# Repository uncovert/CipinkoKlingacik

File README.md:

# ČipinkoKlingáčik

**A socketed Raspberry Pi Pico 2 voltage fault-injection carrier for supervised
hardware research.** Portable project/repository name: `cipinkoklingacik`.

**Release: `v0.1.0-alpha.2` · Hardware: C4 · Engineering prototype.**
The routed design passes static electrical/layout checks. **Firmware is not
implemented; no boards have been built or hardware-qualified.** This is not a
production-ready instrument or a guaranteed bypass of any device protection.

*Generic package models; the Pico is a disclosed form-factor proxy. Socket
height, colours and USB clearance are not mechanically approved.*

## What it provides

- A replaceable **Pico 2** on two 1×20 sockets; USB faces the board edge.
- Separate **MOSFET crowbar** and **3.3 V / 1.8 V current-bounded voltage selector**.
- Target disconnect, passive off discharge, open-drain reset and 3.3 V trigger input.
- Optional UART voltage translation and four-terminal current-measurement pads.
- A 100 × 85 mm, two-layer carrier with four M2.5 mounting positions.

The board uses established circuit techniques and manufacturer/KiCad assets;
it is a custom carrier, **not a fork of PicoGlitcher**. There is no SWD debugger
implementation. An external SWD probe and synchronization software are separate.

## Start here

| Need | Location |
| --- | --- |
| Open the design | [KiCad project](hardware/cipinkoklingacik.kicad_pro) · [hardware guide](hardware/README.md) |
| Read the circuit | [Electrical design](docs/DESIGN.md) · [schematic PDF](hardware/cipinkoklingacik.pdf) |
| Connect a target | [Wiring and SWD overview](docs/CONNECTING.md) |
| View the assembly | [3D views and PDF](hardware/visuals/README.md) |
| Review PCB evidence | [PCB review](hardware/PCB_REVIEW.md) · [review decisions](docs/REVIEW.md) |
| Inspect manufacturing data | [Prototype package](hardware/manufacturing/README.md) |
| Upload to JLCPCB | [Upload files, sourcing review and cost model](docs/JLCPCB.md) |
| Reproduce checks | [Build/check guide](docs/BUILD.md) |
| Understand remaining work | [Qualification checklist](docs/VALIDATION.md) · [parts policy](docs/PARTS.md) |

## Operating boundaries

- **10 mA total downstream load**, including target, bleeders and fitted interfaces.
  Both mux input branches retain **15 Ω** resistors; do not bypass them.
- Initial profiles: ≤100 nF / four dips or ≤1 µF / one dip, ≥20 ms between burst
  starts. At 100 nF the RC settling estimate is ~5.8 µs. **No settled 100 ns /
  100 nF promise.** Source labels are not calibrated target-pin voltages.
- Crowbar and target supply are different connectors. Externally powered crowbar
  targets leave the board's target-supply wire disconnected.
- **ARM ships open. No independent stuck-on timeout is fitted.** Use only
  expendable, authorized targets and qualify first with energy-limited dummy loads.
- Driver operation requires **4.90–5.25 V measured at VDD**. An arbitrary USB
  source/cable is not guaranteed to meet this. No hot-plug or misplug protection.

## Quick verification

```sh
python3 -m unittest discover -s tests -v
python3 scripts/design_calculations.py
```

These dependency-free checks inspect the included sources and exports; they
are **not a fresh KiCad run or hardware validation**. See [BUILD.md](docs/BUILD.md)
for full schematic regeneration, ERC, strict DRC/parity, exports and renders.
Never mix fabrication files from different manifests.

## Release and licensing

[Release notes](docs/RELEASE.md) describe the alpha handoff and local packaging.
Supplier sourcing/rotation, socket/USB fit, firmware, transient, thermal and
waveform qualification remain open. No components or boards have been ordered.

Original hardware is **CERN-OHL-P-2.0**; original software and prose are **MIT**.
Vendored KiCad assets retain their upstream licences and exceptions. See
[LICENSE](LICENSE), [NOTICE.md](NOTICE.md) and [CONTRIBUTING.md](CONTRIBUTING.md).

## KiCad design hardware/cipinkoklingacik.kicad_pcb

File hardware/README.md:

# ČipinkoKlingáčik hardware — C4

**Engineering-prototype design files, not qualified hardware.** Open
[`cipinkoklingacik.kicad_pro`](cipinkoklingacik.kicad_pro) in **KiCad 10**.
The A2 schematic uses named connections and project-local pinned libraries.
No library download is needed to inspect its connectivity.

## Authoritative sources and exports

| Files | Purpose |
| --- | --- |
| `cipinkoklingacik.kicad_pcb` | Authoritative, fully routed PCB; edit in PCB Editor |
| `cipinkoklingacik.kicad_sch` / `.kicad_sym` | Generator-owned schematic/symbols |
| `cipinkoklingacik.kicad_pro`, `fp-lib-table`, `sym-lib-table` | Project/rules/library mapping |
| `CipinkoKlingacik.pretty/`, `vendor/` | Pinned footprints/primitives, provenance and licences |
| [Schematic PDF](cipinkoklingacik.pdf) / [preview](cipinkoklingacik-schematic.png) | Review drawings |
| [Full DRC](cipinkoklingacik-drc.json), [ERC](cipinkoklingacik-erc.rpt), [status](cipinkoklingacik-pcb-status.json) | Static check evidence and source hashes |
| [Connectivity](cipinkoklingacik-connectivity.json), `cipinkoklingacik.net` | Intended contract and actual KiCad export |
| [Baseline BOM](cipinkoklingacik-bom.csv), [all parts](cipinkoklingacik-parts-all.csv) | Exact candidate parts and native DNP state |
| [Manufacturing](manufacturing/README.md) | Baseline Gerber/drill/stencil/BOM/placement package |
| [Visuals](visuals/README.md) | Illustrative assembled/top/bottom/service views |

The board has **92 schematic footprints + four mechanical footprints**.
Baseline population: **68 SMT + seven hand-fit references**, eight bare probe
pads, and nine DNP references: **U8, C18, JP3–JP5, R20, R31, R40, R41**.
R39=0 Ω is fitted. JP2 ARM has **no cap fitted**. Module headers/sockets and loose
caps are separate accessories, not additional SMT rows.

## Source ownership / maintenance

- **PCB:** authoritative and not generator-owned. There is no board-regeneration
  script in this release. Preserve intentional edits; see [BUILD.md](../docs/BUILD.md).
- **Schematic:** edit `scripts/generate_kicad_schematic.py` and
  `scripts/hardware_parts.py`; normal regeneration overwrites schematic, local
  symbols, library tables, connectivity and BOMs. This is not a round-trip editor.
- Stable UUIDs are deliberately retained across the project rename. The legacy
  UUID seed is an internal identifier, not an old project output or PCB generator.
- Footprint upgrades are explicit operations; normal regeneration never updates
  pinned library geometry. Follow [vendor/README.md](vendor/README.md).
- After a PCB edit: run strict checks, refresh return review, rerun strict
  checks, regenerate renders and prototype exports, then run all tests.

## Check interpretation

KiCad 10.0.7 evidence: **ERC 0 errors / 0 warnings**; **PCB DRC 0 violations /
0 unconnected / 0 schematic parity issues**; no ignored PCB checks or exclusions.
The regression suite rejects new ignores and pins the reviewed severity settings.

ERC retains four disclosed standard ignores: single-use global labels, four-way
wire junctions, SPICE-model issues and footprint-filter mismatch. This local-label,
single-sheet, no-SPICE custom-symbol capture does not use global labels or
footprint filters; PCB footprint-filter checking is enabled. Static checks are
not electrical, thermal, assembly or firmware qualification.

## Important net aliases

| Alias | Meaning |
| --- | --- |
| `GL` | Separate crowbar drain — **not** target supply |
| `TVDD` / `T_PRE` | Target supply / pre-shunt supply |
| `VH` / `VL` | High/low upstream reservoirs |
| `MVCC` / `HOLD` | Retained mux supply / its held input |
| `MY0` / `MY1` / `MZ` | Mux input/output nodes |
| `MUX_CMD` / `MUX_S` | GP5 command / mux select |
| `CB_PULSE` / `ARM_EN` | GP2 pulse / GP8 driver arm |
| `TGT_ON` / `REN` | GP4 disconnect / GP10 rail enable |
| `RST_ASSERT` / `RST_T` | Reset control / open-drain target reset |
| `TRIG_IN` / `TRIG_OUT` | Raw trigger input / conditioned GP3 input |
| `UART_OE` / `UVCCB` | GP9 UART disable / isolated UART target reference |
| `ISENSE_P` / `ISENSE_N` | Separate R20 sense terminals; differential probing only |

Full pin allocation, timing and power states are in [DESIGN.md](../docs/DESIGN.md).
Read [PCB_REVIEW.md](PCB_REVIEW.md) and [VALIDATION.md](../docs/VALIDATION.md)
before any order or target connection.

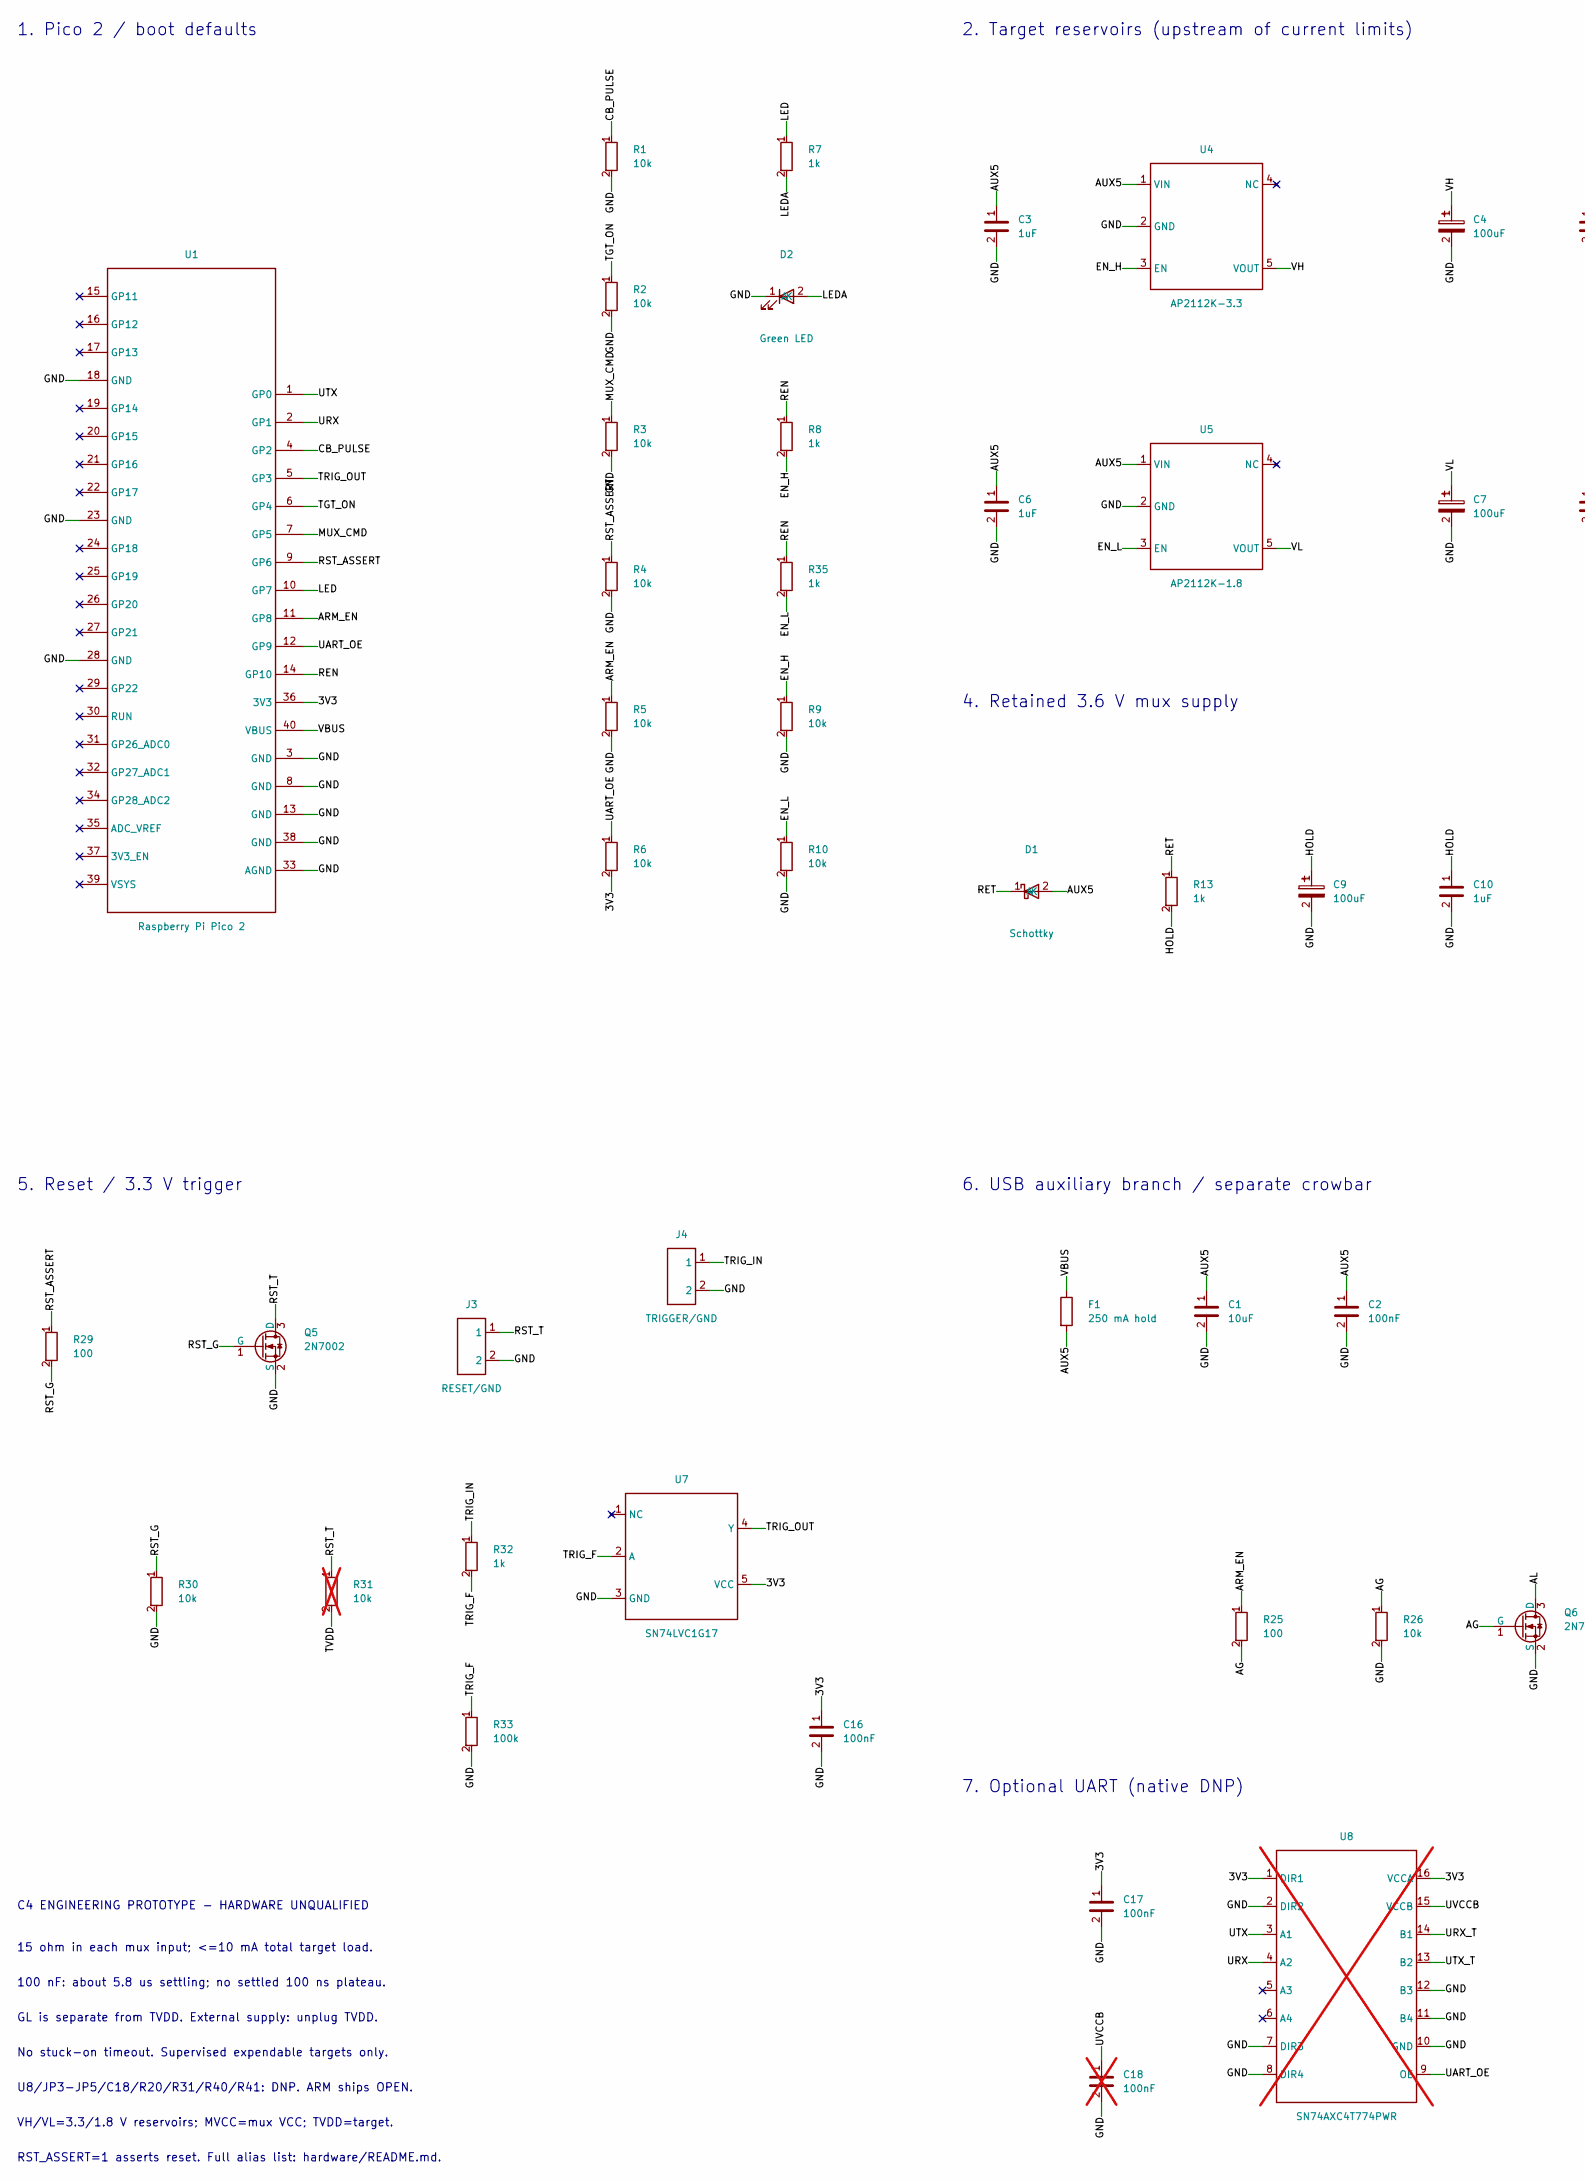
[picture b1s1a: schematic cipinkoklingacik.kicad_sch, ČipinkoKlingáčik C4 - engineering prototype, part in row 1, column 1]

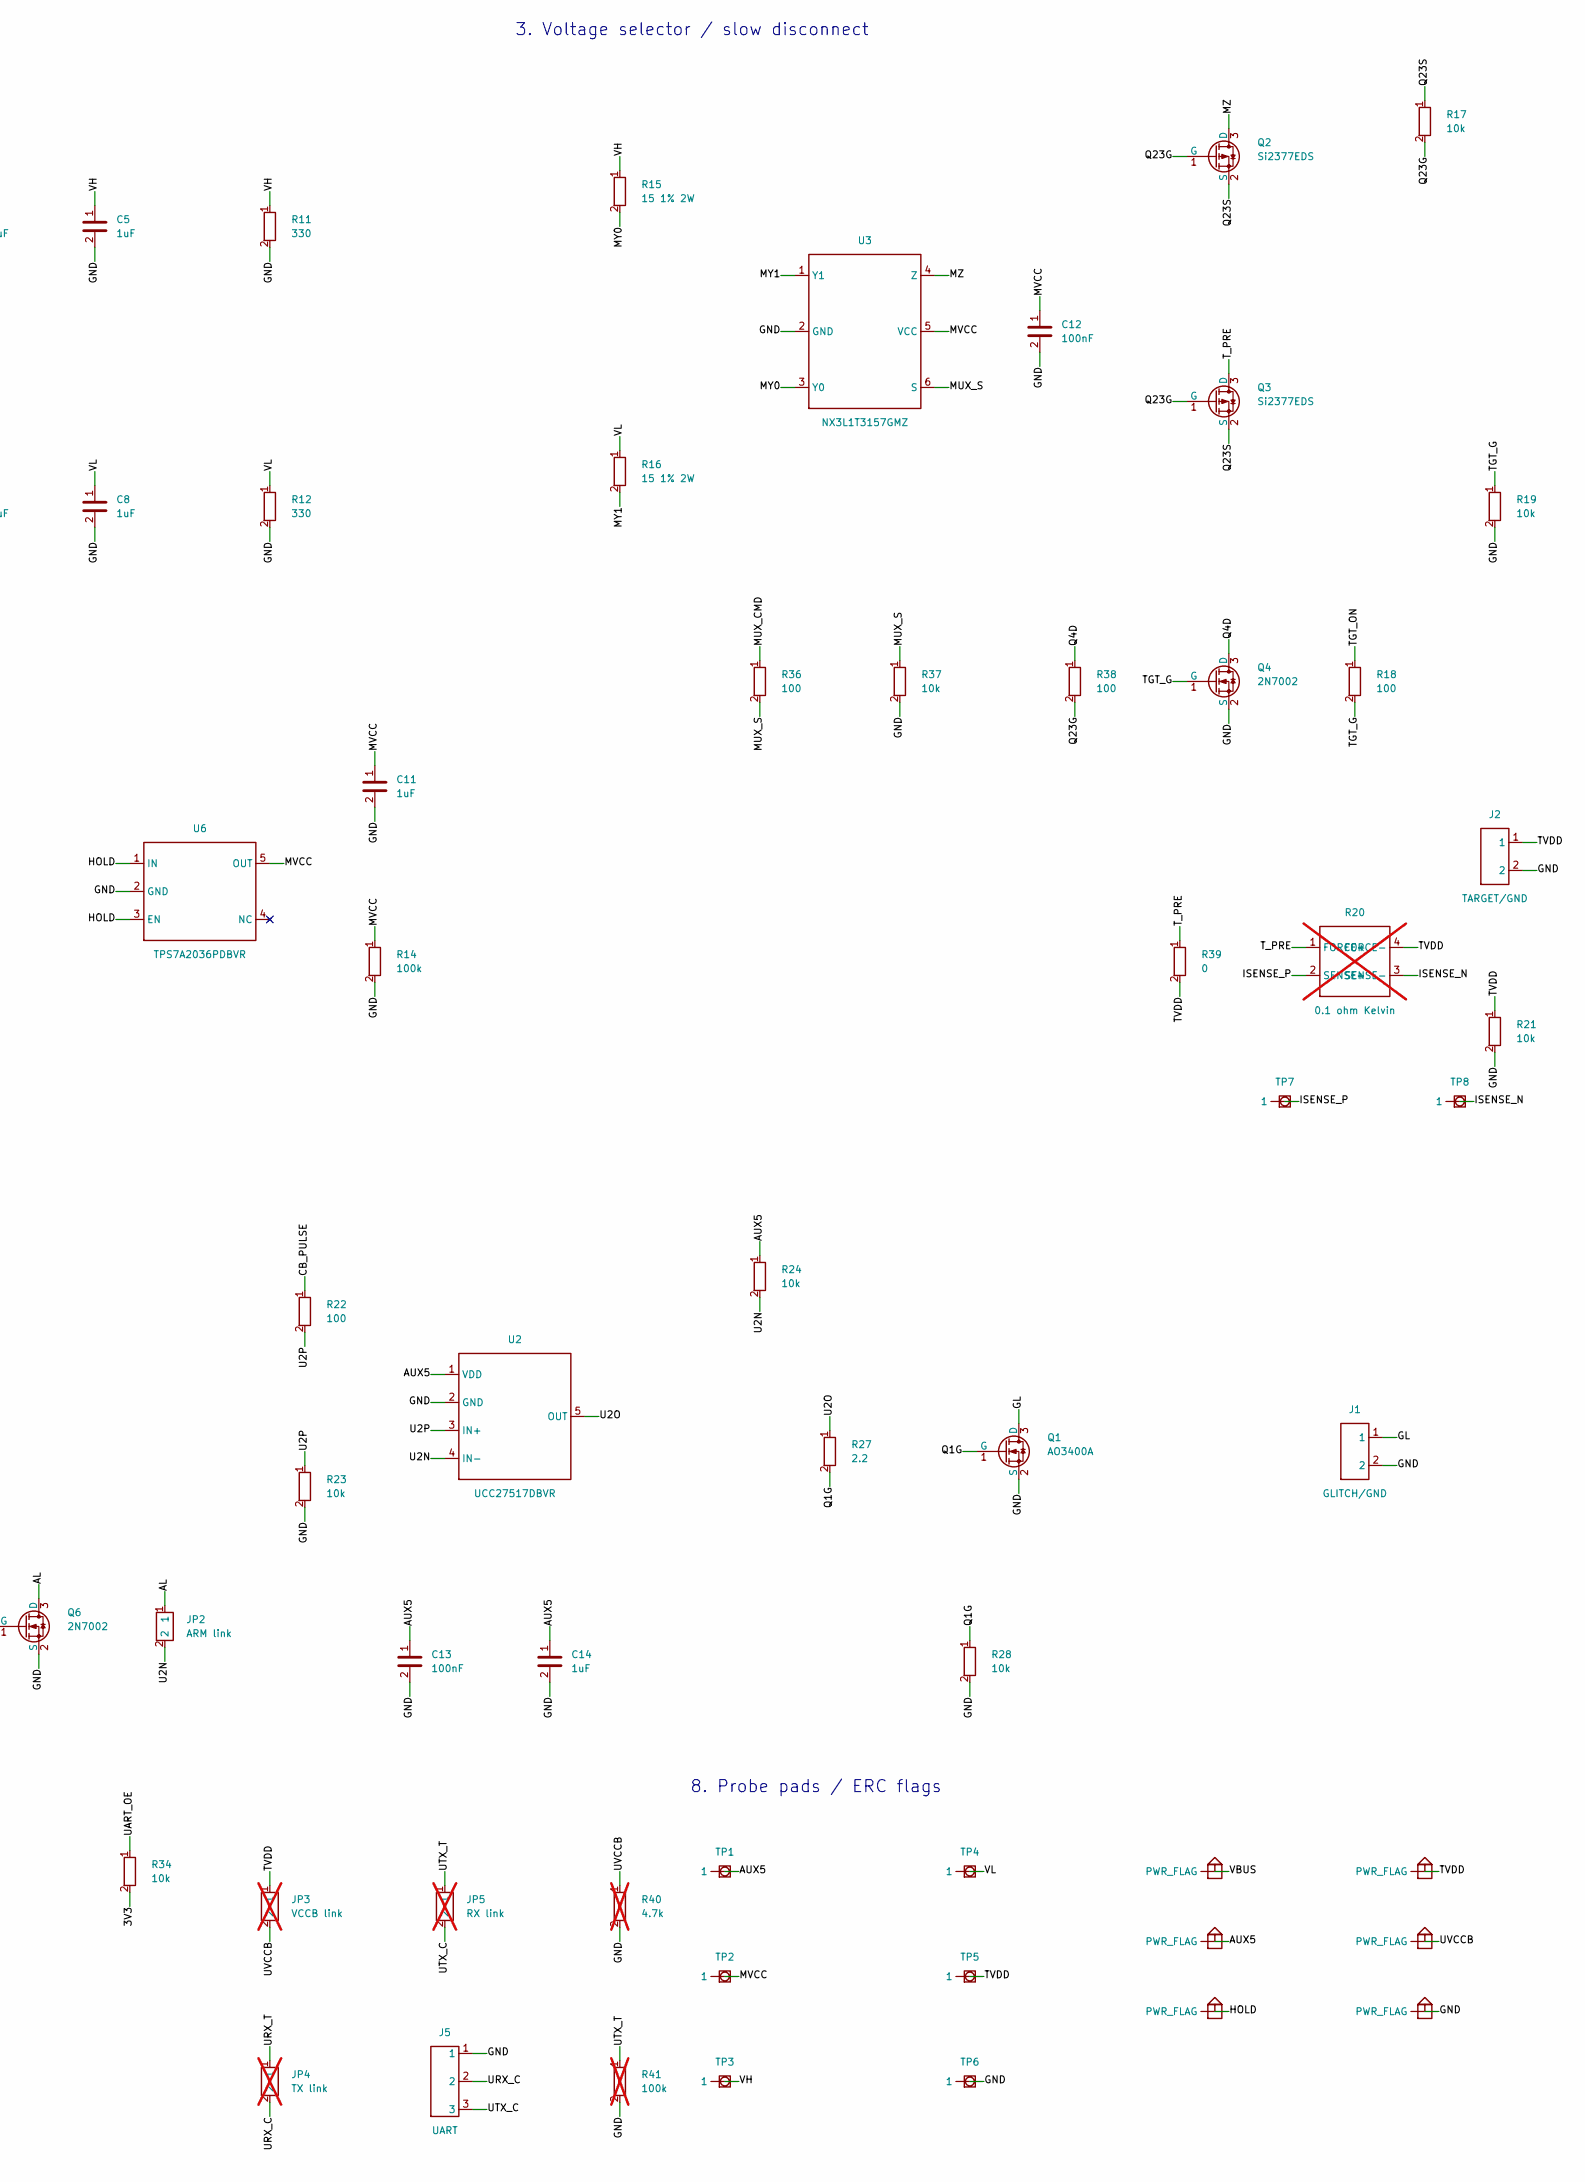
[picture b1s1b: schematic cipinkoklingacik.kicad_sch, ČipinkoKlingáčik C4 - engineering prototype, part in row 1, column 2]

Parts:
C1: 10uF; C_1206_3216Metric; MPN GRM31CR71C106KA12L; LCSC C97954
C2, C12, C13, C16, C17: 100nF; C_0805_2012Metric; MPN CC0805KRX7R9BB104; LCSC C49678
C3, C5, C6, C8, C10, C11, C14: 1uF; C_0805_2012Metric; MPN GRM21BR71C105KA01L; LCSC C77079
C4, C7, C9: 100uF; CP_Elec_6.3x5.8; MPN EEE-FK1C101P; LCSC C128532
C18: 100nF; C_0805_2012Metric; MPN CC0805KRX7R9BB104; LCSC C49678; not fitted
D1: Schottky; D_SOD-323; MPN BAT54WS-7-F; LCSC C124205
D2: Green LED; LED_0805_2012Metric; MPN LTST-C170KGKT; LCSC C98221
F1: 250 mA hold; Fuse_1206_3216Metric; MPN 1206L025YR; LCSC C99561
J1: GLITCH/GND; PinHeader_1x02_P2.54mm_Vertical; MPN TSW-102-07-G-S
J2: TARGET/GND; PinHeader_1x02_P2.54mm_Vertical; MPN TSW-102-07-G-S
J3: RESET/GND; PinHeader_1x02_P2.54mm_Vertical; MPN TSW-102-07-G-S
J4: TRIGGER/GND; PinHeader_1x02_P2.54mm_Vertical; MPN TSW-102-07-G-S
J5: UART; PinHeader_1x03_P2.54mm_Vertical; MPN TSW-103-07-G-S
JP2: ARM link; PinHeader_1x02_P2.54mm_Vertical; MPN TSW-102-07-G-S
JP3: VCCB link; PinHeader_1x02_P2.54mm_Vertical; MPN TSW-102-07-G-S; not fitted
JP4: TX link; PinHeader_1x02_P2.54mm_Vertical; MPN TSW-102-07-G-S; not fitted
JP5: RX link; PinHeader_1x02_P2.54mm_Vertical; MPN TSW-102-07-G-S; not fitted
Q1: AO3400A; SOT-23; MPN AO3400A; LCSC C20917
Q2, Q3: Si2377EDS; SOT-23; MPN Si2377EDS-T1-GE3; LCSC C143698
Q4, Q5, Q6: 2N7002; SOT-23; MPN 2N7002,215; LCSC C65189
R1, R2, R3, R4, R5, R6, R9, R10, R17, R19, R21, R23, R24, R26, R28, R30, R34, R37: 10k; R_0805_2012Metric; MPN 0805W8F1002T5E; LCSC C17414
R7, R8, R13, R32, R35: 1k; R_0805_2012Metric; MPN 0805W8F1001T5E; LCSC C17513
R11, R12: 330; R_0805_2012Metric; MPN 0805W8F3300T5E; LCSC C17630
R14, R33: 100k; R_0805_2012Metric; MPN 0805W8F1003T5E; LCSC C149504
R15, R16: 15 1% 2W; R_2512_6332Metric; MPN RC2512FK-7W15RL; LCSC C6639259
R18, R22, R25, R29, R36, R38: 100; R_0805_2012Metric; MPN 0805W8F1000T5E; LCSC C17408
R20: 0.1 ohm Kelvin; R_Shunt_Vishay_WSK2512_6332Metric_T1.19mm; MPN WSK2512R1000FEA; not fitted
R27: 2.2; R_0805_2012Metric; MPN 0805W8F220KT5E; LCSC C17521
R31: 10k; R_0805_2012Metric; MPN 0805W8F1002T5E; LCSC C17414; not fitted
R39: 0; R_1206_3216Metric; MPN 1206W4F0000T5E; LCSC C17888
R40: 4.7k; R_0805_2012Metric; MPN RC0805FR-074K7L; not fitted
R41: 100k; R_0805_2012Metric; MPN RC0805FR-07100KL; not fitted
TP1: AUX_5V; TestPoint_Pad_D1.5mm; MPN PCB_PAD
TP2: MUX_VCC; TestPoint_Pad_D1.5mm; MPN PCB_PAD
TP3: VHIGH; TestPoint_Pad_D1.5mm; MPN PCB_PAD
TP4: VLOW; TestPoint_Pad_D1.5mm; MPN PCB_PAD
TP5: TARGET_VDD; TestPoint_Pad_D1.5mm; MPN PCB_PAD
TP6: GND; TestPoint_Pad_D1.5mm; MPN PCB_PAD
TP7: ISENSE_P; TestPoint_Pad_D1.5mm; MPN PCB_PAD
TP8: ISENSE_N; TestPoint_Pad_D1.5mm; MPN PCB_PAD
U1: Raspberry Pi Pico 2; RaspberryPi_Pico_Common_THT; MPN SC1631
U2: UCC27517DBVR; SOT-23-5; MPN UCC27517DBVR; LCSC C99395
U3: NX3L1T3157GMZ; SOT-886; MPN NX3L1T3157GMZ; LCSC C1870392
U4: AP2112K-3.3; SOT-23-5; MPN AP2112K-3.3TRG1; LCSC C51118
U5: AP2112K-1.8; SOT-23-5; MPN AP2112K-1.8TRG1; LCSC C176944
U6: TPS7A2036PDBVR; SOT-23-5; MPN TPS7A2036PDBVR; LCSC C2873626
U7: SN74LVC1G17; SOT-23-5; MPN SN74LVC1G17DBVR; LCSC C7836
U8: SN74AXC4T774PWR; TSSOP-16_4.4x5mm_P0.65mm; MPN SN74AXC4T774PWR; not fitted

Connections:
/3V3: C16.1, C17.1, R6.2, R34.2, U1.36 (3V3), U7.5 (VCC), U8.1 (DIR1), U8.16 (VCCA)
/AG: Q6.1 (G), R25.2, R26.1
/AL: JP2.1, Q6.3 (D)
/ARM_EN: R5.1, R25.1, U1.11 (GP8)
/AUX5: C1.1, C2.1, C3.1, C6.1, C13.1, C14.1, D1.2 (A), F1.2, R24.1, TP1.1, U2.1 (VDD), U4.1 (VIN), U5.1 (VIN)
/CB_PULSE: R1.1, R22.1, U1.4 (GP2)
/EN_H: R8.2, R9.1, U4.3 (EN)
/EN_L: R10.1, R35.2, U5.3 (EN)
/GL: J1.1, Q1.3 (D)
/GND: C1.2, C2.2, C3.2, C4.2, C5.2, C6.2, C7.2, C8.2, C9.2, C10.2, C11.2, C12.2, C13.2, C14.2, C16.2, C17.2, C18.2, D2.1 (K), J1.2, J2.2, J3.2, J4.2, J5.1, Q1.2 (S), Q4.2 (S), Q5.2 (S), Q6.2 (S), R1.2, R2.2, R3.2, R4.2, R5.2, R9.2, R10.2, R11.2, R12.2, R14.2, R19.2, R21.2, R23.2, R26.2, R28.2, R30.2, R33.2, R37.2, R40.2, R41.2, TP6.1, U1.3 (GND), U1.8 (GND), U1.13 (GND), U1.18 (GND), U1.23 (GND), U1.28 (GND), U1.33 (AGND), U1.38 (GND), U2.2 (GND), U3.2 (GND), U4.2 (GND), U5.2 (GND), U6.2 (GND), U7.3 (GND), U8.2 (DIR2), U8.7 (DIR3), U8.8 (DIR4), U8.10 (GND), U8.11 (B4), U8.12 (B3)
/HOLD: C9.1, C10.1, R13.2, U6.1 (IN), U6.3 (EN)
/ISENSE_N: R20.3 (SENSE-), TP8.1
/ISENSE_P: R20.2 (SENSE+), TP7.1
/LED: R7.1, U1.10 (GP7)
/LEDA: D2.2 (A), R7.2
/MUX_CMD: R3.1, R36.1, U1.7 (GP5)
/MUX_S: R36.2, R37.1, U3.6 (S)
/MVCC: C11.1, C12.1, R14.1, TP2.1, U3.5 (VCC), U6.5 (OUT)
/MY0: R15.2, U3.3 (Y0)
/MY1: R16.2, U3.1 (Y1)
/MZ: Q2.3 (D), U3.4 (Z)
/Q1G: Q1.1 (G), R27.2, R28.1
/Q4D: Q4.3 (D), R38.1
/Q23G: Q2.1 (G), Q3.1 (G), R17.2, R38.2
/Q23S: Q2.2 (S), Q3.2 (S), R17.1
/REN: R8.1, R35.1, U1.14 (GP10)
/RET: D1.1 (K), R13.1
/RST_ASSERT: R4.1, R29.1, U1.9 (GP6)
/RST_G: Q5.1 (G), R29.2, R30.1
/RST_T: J3.1, Q5.3 (D), R31.1
/TGT_G: Q4.1 (G), R18.2, R19.1
/TGT_ON: R2.1, R18.1, U1.6 (GP4)
/TRIG_F: R32.2, R33.1, U7.2 (A)
/TRIG_IN: J4.1, R32.1
/TRIG_OUT: U1.5 (GP3), U7.4 (Y)
/TVDD: J2.1, JP3.1, R20.4 (FORCE-), R21.1, R31.2, R39.2, TP5.1
/T_PRE: Q3.3 (D), R20.1 (FORCE+), R39.1
/U2N: JP2.2, R24.2, U2.4 (IN-)
/U2O: R27.1, U2.5 (OUT)
/U2P: R22.2, R23.1, U2.3 (IN+)
/UART_OE: R6.1, R34.1, U1.12 (GP9), U8.9 (OE)
/URX: U1.2 (GP1), U8.4 (A2)
/URX_C: J5.2, JP4.2
/URX_T: JP4.1, U8.14 (B1)
/UTX: U1.1 (GP0), U8.3 (A1)
/UTX_C: J5.3, JP5.2
/UTX_T: JP5.1, R41.1, U8.13 (B2)
/UVCCB: C18.1, JP3.2, R40.1, U8.15 (VCCB)
/VBUS: F1.1, U1.40 (VBUS)
/VH: C4.1, C5.1, R11.1, R15.1, TP3.1, U4.5 (VOUT)
/VL: C7.1, C8.1, R12.1, R16.1, TP4.1, U5.5 (VOUT)

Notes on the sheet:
1. Pico 2 / boot defaults
2. Target reservoirs (upstream of current limits)
3. Voltage selector / slow disconnect
4. Retained 3.6 V mux supply
5. Reset / 3.3 V trigger
6. USB auxiliary branch / separate crowbar
7. Optional UART (native DNP)
8. Probe pads / ERC flags
C4 ENGINEERING PROTOTYPE - HARDWARE UNQUALIFIED
15 ohm in each mux input; <=10 mA total target load.
100 nF: about 5.8 us settling; no settled 100 ns plateau.
GL is separate from TVDD. External supply: unplug TVDD.
No stuck-on timeout. Supervised expendable targets only.
U8/JP3-JP5/C18/R20/R31/R40/R41: DNP. ARM ships OPEN.
VH/VL=3.3/1.8 V reservoirs; MVCC=mux VCC; TVDD=target.
RST_ASSERT=1 asserts reset. Full alias list: hardware/README.md.

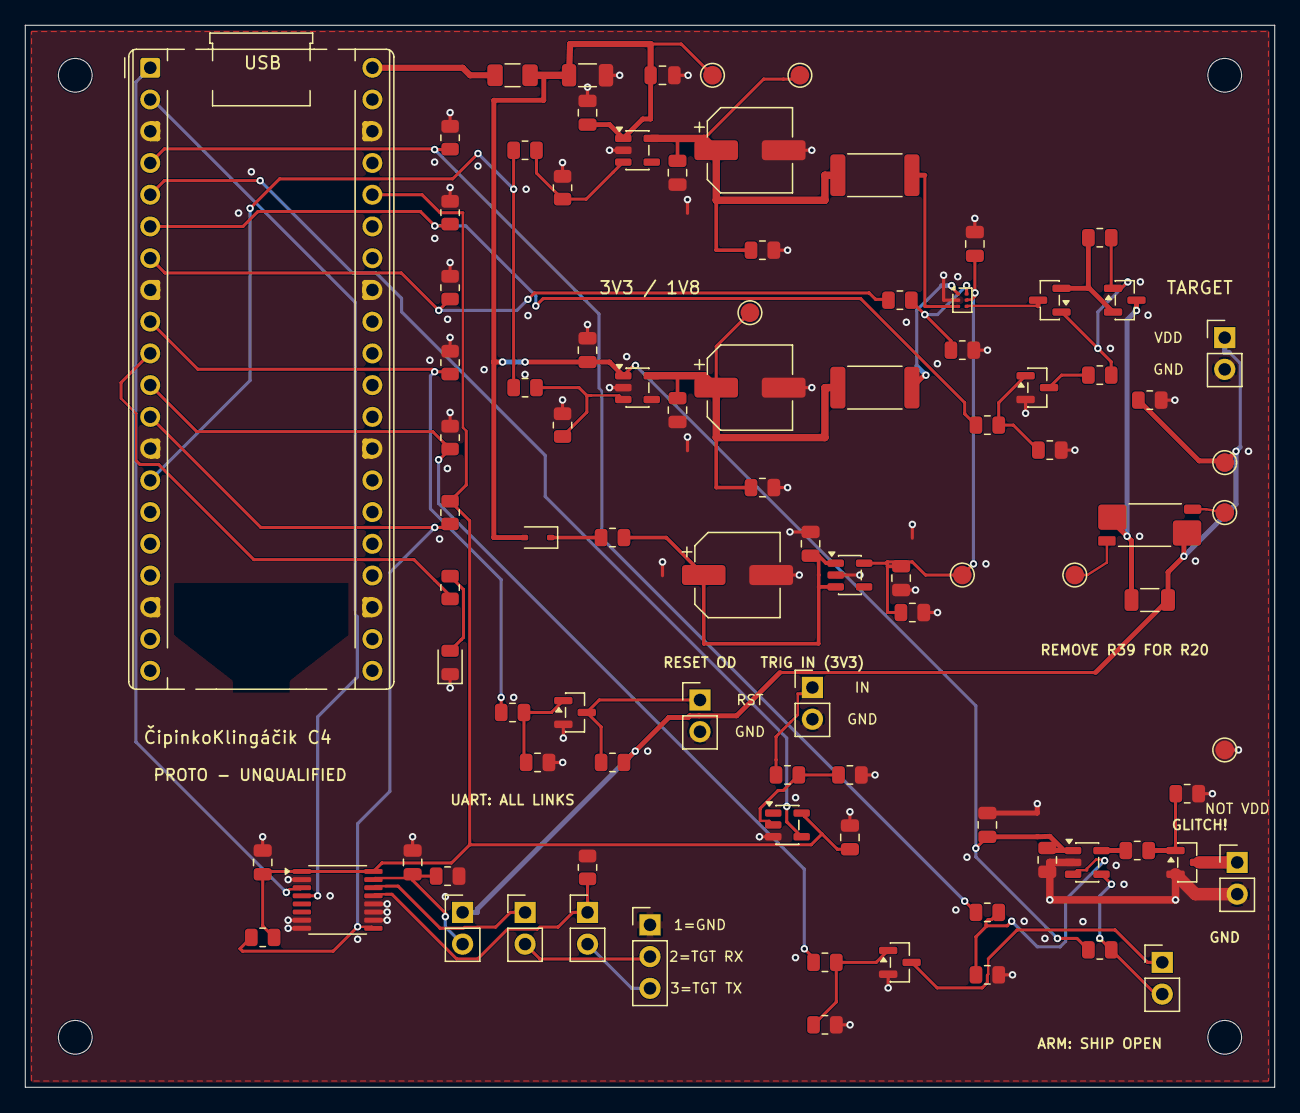
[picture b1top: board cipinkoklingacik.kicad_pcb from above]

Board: 2 copper layers, 100.0 x 85.0 mm, 96 parts (0 on the bottom side), 51 nets.

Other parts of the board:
H1, H2, H3, H4: M2.5 NPTH; MountingHole_2.7mm_M2.5

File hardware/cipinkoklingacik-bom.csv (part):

Reference,Value,MPN,Manufacturer,Footprint,DNP,Assembly,Requirement,Datasheet,LCSC
U1,Raspberry Pi Pico 2,SC1631,Raspberry Pi,CipinkoKlingacik:RaspberryPi_Pico_Common_THT,no,Module/hand-fit,Pico 2 without headers; hand-fit 2x 1x20 sockets and module headers,https://datasheets.raspberrypi.com/pico/pico-2-datasheet.pdf,
R1,10k,0805W8F1002T5E,UNI-ROYAL,CipinkoKlingacik:R_0805_2012Metric,no,SMT,"1%, 0.125 W; gate pulse rating requires check",https://www.lcsc.com/datasheet/lcsc_datasheet_2411221126_UNI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,C17414
R2,10k,0805W8F1002T5E,UNI-ROYAL,CipinkoKlingacik:R_0805_2012Metric,no,SMT,"1%, 0.125 W; gate pulse rating requires check",https://www.lcsc.com/datasheet/lcsc_datasheet_2411221126_UNI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,C17414
R3,10k,0805W8F1002T5E,UNI-ROYAL,CipinkoKlingacik:R_0805_2012Metric,no,SMT,"1%, 0.125 W; gate pulse rating requires check",https://www.lcsc.com/datasheet/lcsc_datasheet_2411221126_UNI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,C17414
R4,10k,0805W8F1002T5E,UNI-ROYAL,CipinkoKlingacik:R_0805_2012Metric,no,SMT,"1%, 0.125 W; gate pulse rating requires check",https://www.lcsc.com/datasheet/lcsc_datasheet_2411221126_UNI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,C17414
R5,10k,0805W8F1002T5E,UNI-ROYAL,CipinkoKlingacik:R_0805_2012Metric,no,SMT,"1%, 0.125 W; gate pulse rating requires check",https://www.lcsc.com/datasheet/lcsc_datasheet_2411221126_UNI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,C17414
R6,10k,0805W8F1002T5E,UNI-ROYAL,CipinkoKlingacik:R_0805_2012Metric,no,SMT,"1%, 0.125 W; gate pulse rating requires check",https://www.lcsc.com/datasheet/lcsc_datasheet_2411221126_UNI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,C17414
R7,1k,0805W8F1001T5E,UNI-ROYAL,CipinkoKlingacik:R_0805_2012Metric,no,SMT,"1%, 0.125 W; gate pulse rating requires check",https://www.lcsc.com/datasheet/lcsc_datasheet_2411221126_UNI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,C17513
D2,Green LED,LTST-C170KGKT,Lite-On,CipinkoKlingacik:LED_0805_2012Metric,no,SMT,Green LED; K1 A2; software status only,https://optoelectronics.liteon.com/upload/download/DS22-2000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,C98221
R8,1k,0805W8F1001T5E,UNI-ROYAL,CipinkoKlingacik:R_0805_2012Metric,no,SMT,"1%, 0.125 W; gate pulse rating requires check",https://www.lcsc.com/datasheet/lcsc_datasheet_2411221126_UNI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,C17513
R9,10k,0805W8F1002T5E,UNI-ROYAL,CipinkoKlingacik:R_0805_2012Metric,no,SMT,"1%, 0.125 W; gate pulse rating requires check",https://www.lcsc.com/datasheet/lcsc_datasheet_2411221126_UNI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,C17414
R10,10k,0805W8F1002T5E,UNI-ROYAL,CipinkoKlingacik:R_0805_2012Metric,no,SMT,"1%, 0.125 W; gate pulse rating requires check",https://www.lcsc.com/datasheet/lcsc_datasheet_2411221126_UNI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,C17414
R35,1k,0805W8F1001T5E,UNI-ROYAL,CipinkoKlingacik:R_0805_2012Metric,no,SMT,"1%, 0.125 W; gate pulse rating requires check",https://www.lcsc.com/datasheet/lcsc_datasheet_2411221126_UNI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,C17513
F1,250 mA hold,1206L025YR,Littelfuse,CipinkoKlingacik:Fuse_1206_3216Metric,no,SMT,"250 mA hold, 500 mA trip, 16 V PTC; 100 A fault rating; R1max 2.3 ohm; 80 ms max trip at 8 A, NOT precision limiting; qualify inrush/drop",https://www.lcsc.com/datasheet/lcsc_datasheet_2304140030_Lit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,C99561
C1,10uF,GRM31CR71C106KA12L,Murata,CipinkoKlingacik:C_1206_3216Metric,no,SMT,"10 uF, 16 V, X7R, 10%; check DC bias",https://www.murata.com/en-us/products/capacitor/mlcc,C97954
C2,100nF,CC0805KRX7R9BB104,Yageo,CipinkoKlingacik:C_0805_2012Metric,no,SMT,"100 nF, 50 V, X7R, 10%",https://www.lcsc.com/datasheet/lcsc_datasheet_2304140030_YAG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,C49678
U2,UCC27517DBVR,UCC27517DBVR,Texas Instruments,CipinkoKlingacik:SOT-23-5,no,SMT,4.90-5.25 V measured at VDD before arm,https://www.ti.com/lit/ds/symlink/ucc27517.pdf,C99395
C13,100nF,CC0805KRX7R9BB104,Yageo,CipinkoKlingacik:C_0805_2012Metric,no,SMT,"100 nF, 50 V, X7R, 10%",https://www.lcsc.com/datasheet/lcsc_datasheet_2304140030_YAG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,C49678
C14,1uF,GRM21BR71C105KA01L,Murata,CipinkoKlingacik:C_0805_2012Metric,no,SMT,"1 uF, 16 V, X7R, 10%; verify >=0.47 uF at bias",https://www.murata.com/en-us/products/capacitor/mlcc,C77079
R22,100,0805W8F1000T5E,UNI-ROYAL,CipinkoKlingacik:R_0805_2012Metric,no,SMT,"1%, 0.125 W; gate pulse rating requires check",https://www.lcsc.com/datasheet/lcsc_datasheet_2411221126_UNI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,C17408
R23,10k,0805W8F1002T5E,UNI-ROYAL,CipinkoKlingacik:R_0805_2012Metric,no,SMT,"1%, 0.125 W; gate pulse rating requires check",https://www.lcsc.com/datasheet/lcsc_datasheet_2411221126_UNI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,C17414
R24,10k,0805W8F1002T5E,UNI-ROYAL,CipinkoKlingacik:R_0805_2012Metric,no,SMT,"1%, 0.125 W; gate pulse rating requires check",https://www.lcsc.com/datasheet/lcsc_datasheet_2411221126_UNI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,C17414
Q6,2N7002,"2N7002,215",Nexperia,CipinkoKlingacik:SOT-23,no,SMT,G1 S2 D3,https://assets.nexperia.com/documents/data-sheet/2N7002.pdf,C65189
R25,100,0805W8F1000T5E,UNI-ROYAL,CipinkoKlingacik:R_0805_2012Metric,no,SMT,"1%, 0.125 W; gate pulse rating requires check",https://www.lcsc.com/datasheet/lcsc_datasheet_2411221126_UNI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,C17408
R26,10k,0805W8F1002T5E,UNI-ROYAL,CipinkoKlingacik:R_0805_2012Metric,no,SMT,"1%, 0.125 W; gate pulse rating requires check",https://www.lcsc.com/datasheet/lcsc_datasheet_2411221126_UNI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,C17414
JP2,ARM link,TSW-102-07-G-S,Samtec,CipinkoKlingacik:PinHeader_1x02_P2.54mm_Vertical,no,THT/hand-fit,2.54 mm header; pin1 marked; hand-fit; removable shunts separate,https://suddendocs.samtec.com/catalog_english/tsw.pdf,
Q1,AO3400A,AO3400A,Alpha & Omega Semiconductor,CipinkoKlingacik:SOT-23,no,SMT,G1 S2 D3; pulse/thermal qualification required,https://aosmd.com/sites/default/files/res/datasheets/AO3400A.pdf,C20917
R27,2.2,0805W8F220KT5E,UNI-ROYAL,CipinkoKlingacik:R_0805_2012Metric,no,SMT,"1%, 0.125 W; gate pulse rating requires check",https://www.lcsc.com/datasheet/lcsc_datasheet_2411221126_UNI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,C17521
R28,10k,0805W8F1002T5E,UNI-ROYAL,CipinkoKlingacik:R_0805_2012Metric,no,SMT,"1%, 0.125 W; gate pulse rating requires check",https://www.lcsc.com/datasheet/lcsc_datasheet_2411221126_UNI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,C17414
J1,GLITCH/GND,TSW-102-07-G-S,Samtec,CipinkoKlingacik:PinHeader_1x02_P2.54mm_Vertical,no,THT/hand-fit,2.54 mm header; pin1 marked; hand-fit; removable shunts separate,https://suddendocs.samtec.com/catalog_english/tsw.pdf,
D1,Schottky,BAT54WS-7-F,Diodes Incorporated,CipinkoKlingacik:D_SOD-323,no,SMT,K1 A2; low-current hold-up charging diode,https://www.diodes.com/assets/Datasheets/BAT54WS.pdf,C124205
R13,1k,0805W8F1001T5E,UNI-ROYAL,CipinkoKlingacik:R_0805_2012Metric,no,SMT,"1%, 0.125 W; gate pulse rating requires check",https://www.lcsc.com/datasheet/lcsc_datasheet_2411221126_UNI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,C17513
C9,100uF,EEE-FK1C101P,Panasonic,CipinkoKlingacik:CP_Elec_6.3x5.8,no,SMT,"100 uF 16 V +/-20%, positive pad1; leakage max16 uA; reservoir/hold-up qualification",https://industrial.panasonic.com/cdbs/www-data/pdf/RDE0000/A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,C128532
C10,1uF,GRM21BR71C105KA01L,Murata,CipinkoKlingacik:C_0805_2012Metric,no,SMT,"1 uF, 16 V, X7R, 10%; verify >=0.47 uF at bias",https://www.murata.com/en-us/products/capacitor/mlcc,C77079
U6,TPS7A2036PDBVR,TPS7A2036PDBVR,Texas Instruments,CipinkoKlingacik:SOT-23-5,no,SMT,"3.6 V; IN1 GND2 EN3 NC4 OUT5; EN tied to HOLD_IN, not Pico/AUX5; >=0.47 uF effective output; qualify retention/shutdown",https://www.ti.com/lit/ds/symlink/tps7a20.pdf,C2873626
C11,1uF,GRM21BR71C105KA01L,Murata,CipinkoKlingacik:C_0805_2012Metric,no,SMT,"1 uF, 16 V, X7R, 10%; verify >=0.47 uF at bias",https://www.murata.com/en-us/products/capacitor/mlcc,C77079
R14,100k,0805W8F1003T5E,UNI-ROYAL,CipinkoKlingacik:R_0805_2012Metric,no,SMT,"1%, 0.125 W; gate pulse rating requires check",https://www.lcsc.com/datasheet/lcsc_datasheet_2411221126_UNI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,C149504
U4,AP2112K-3.3,AP2112K-3.3TRG1,Diodes Incorporated,CipinkoKlingacik:SOT-23-5,no,SMT,3.3 V; verify reservoir startup and stability,https://www.diodes.com/assets/Datasheets/AP2112.pdf,C51118
C3,1uF,GRM21BR71C105KA01L,Murata,CipinkoKlingacik:C_0805_2012Metric,no,SMT,"1 uF, 16 V, X7R, 10%; verify >=0.47 uF at bias",https://www.murata.com/en-us/products/capacitor/mlcc,C77079
C4,100uF,EEE-FK1C101P,Panasonic,CipinkoKlingacik:CP_Elec_6.3x5.8,no,SMT,"100 uF 16 V +/-20%, positive pad1; leakage max16 uA; reservoir/hold-up qualification",https://industrial.panasonic.com/cdbs/www-data/pdf/RDE0000/A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,C128532
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
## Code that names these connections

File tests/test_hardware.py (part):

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                         {str(i) for i in range(1, 41)})
        for pin in (3, 8, 13, 18, 23, 28, 33, 38):
            self.assertEqual(self.net("U1", pin), "GND")
        for pin, net in {1: "UTX", 2: "URX", 4: "CB_PULSE", 5: "TRIG_OUT",
                         6: "TGT_ON", 7: "MUX_CMD", 9: "RST_ASSERT", 10: "LED",
                         11: "ARM_EN", 12: "UART_OE", 14: "REN", 36: "3V3", 40: "VBUS"}.items():
            self.assertEqual(self.net("U1", pin), net)
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            self.assertEqual((self.net(ref, 1), self.net(ref, 2)), ("UART_OE", "3V3"))
        self.assertEqual(self.net("C18", 1), self.net("U8", 15))
        self.assertNotEqual(self.net("C18", 1), self.net("J2", 1))
        for pin, net in {1: "3V3", 2: "GND", 3: "UTX", 4: "URX",
                         7: "GND", 8: "GND", 9: "UART_OE", 10: "GND",
                         11: "GND", 12: "GND", 13: "UTX_T", 14: "URX_T",
                         15: "UVCCB", 16: "3V3"}.items():
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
